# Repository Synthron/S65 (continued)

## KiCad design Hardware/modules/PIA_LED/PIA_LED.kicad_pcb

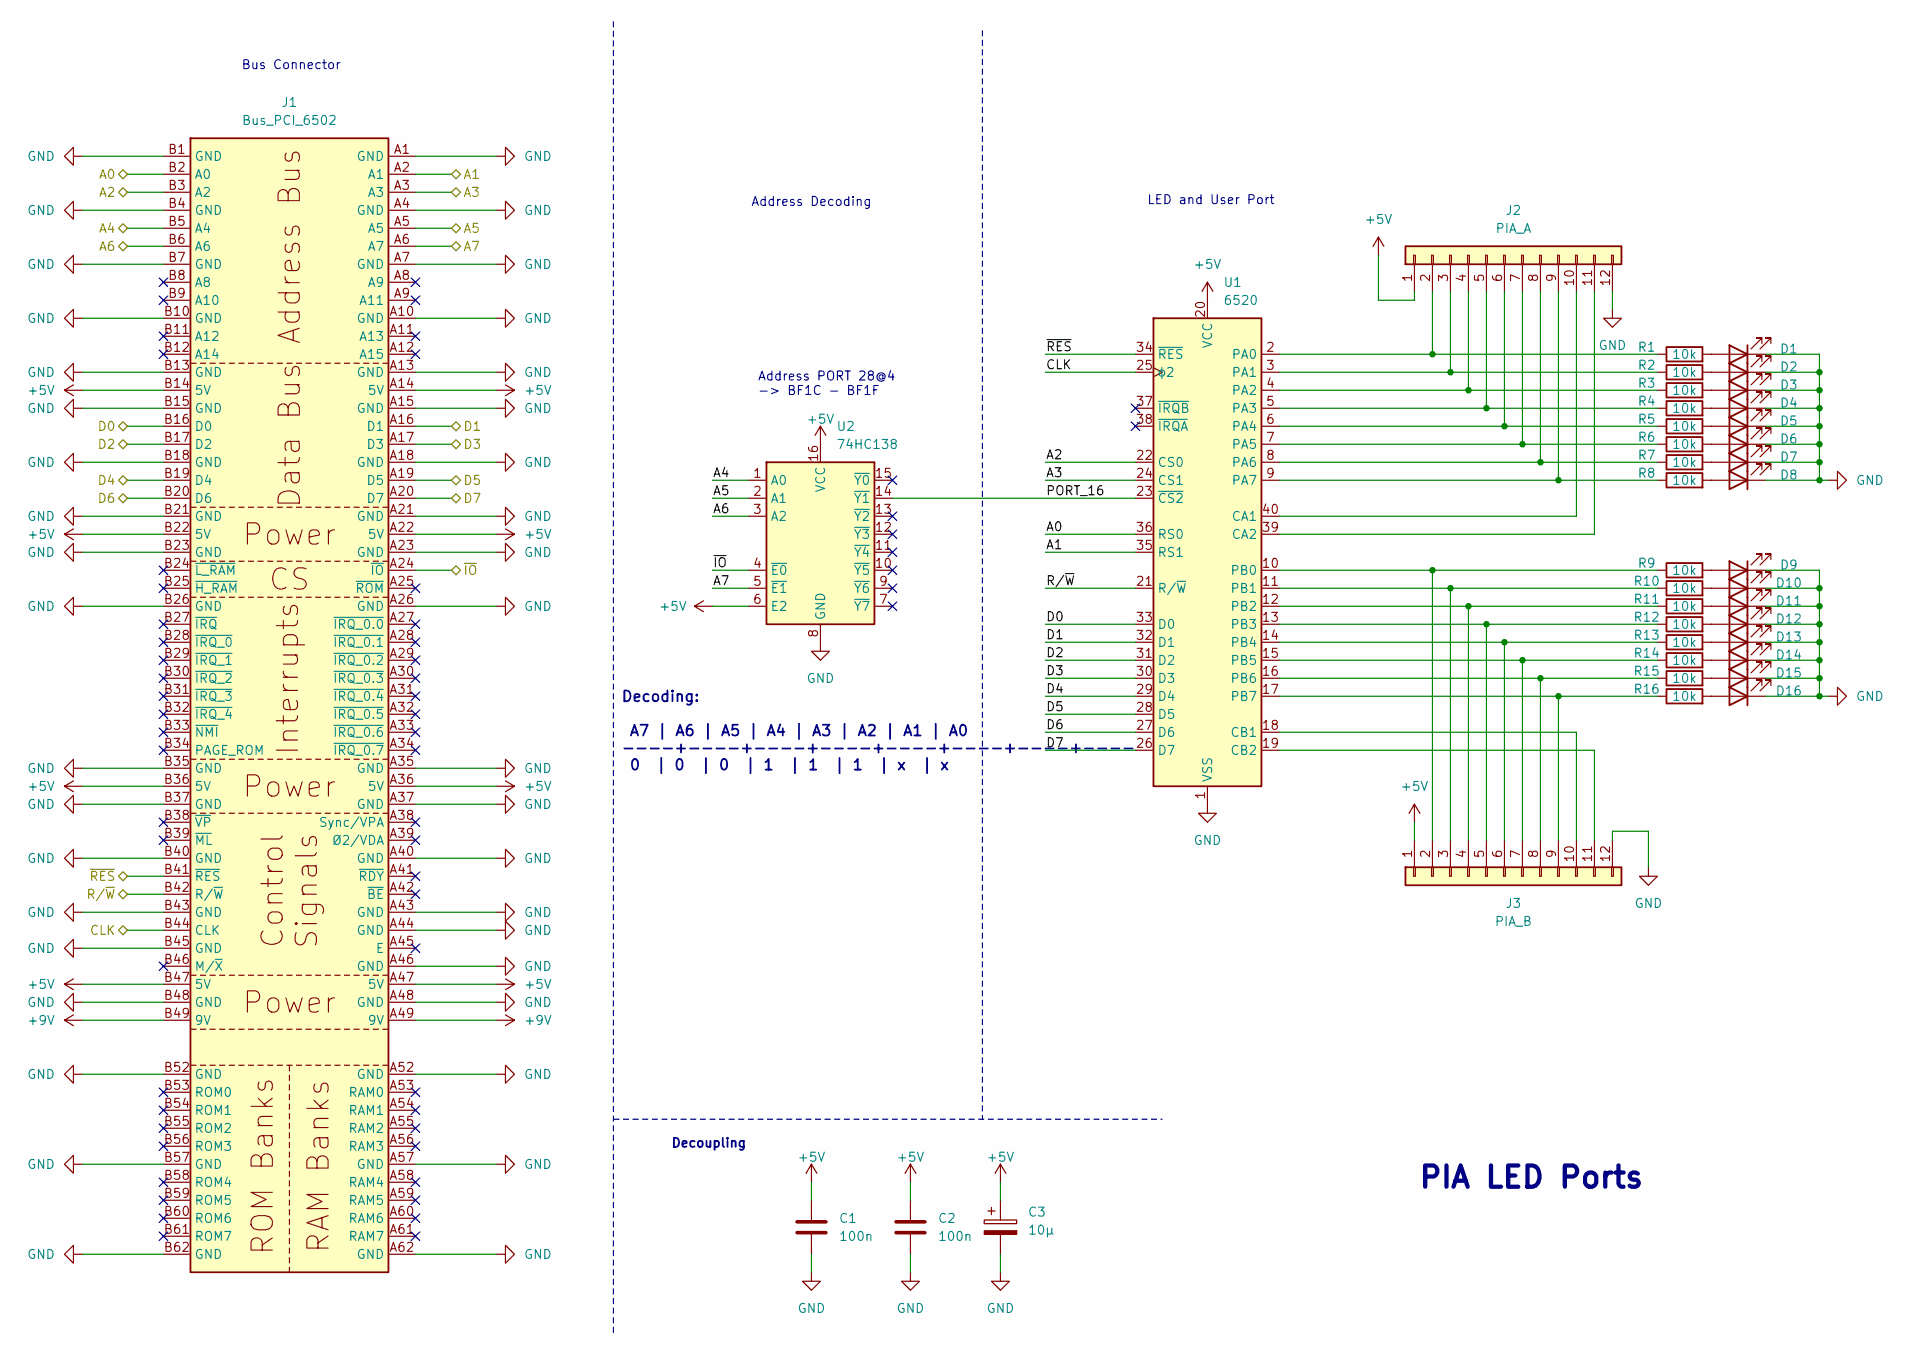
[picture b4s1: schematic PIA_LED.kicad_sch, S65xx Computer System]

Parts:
C1, C2: 100n; C_0805_2012Metric
C3: 10µ; CP_Radial_D5.0mm_P2.50mm
D1, D2, D3, D4, D5, D6, D7, D8, D9, D10, D11, D12, D13, D14, D15, D16: LED; SPST_Edge
J1: Bus_PCI_6502; BUS_PCI
J2: PIA_A; PinHeader_1x12_P2.54mm_Vertical
J3: PIA_B; PinHeader_1x12_P2.54mm_Vertical
R1, R2, R3, R4, R5, R6, R7, R8, R9, R10, R11, R12, R13, R14, R15, R16: 10k; R_0805_2012Metric
U1: 6520; DIP-40_W15.24mm
U2: 74HC138; DIP-16_W7.62mm_LongPads

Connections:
+5V: C1.1, C2.1, C3.1, J1.A14 (5V), J1.A22 (5V), J1.A36 (5V), J1.A47 (5V), J1.B14 (5V), J1.B22 (5V), J1.B36 (5V), J1.B47 (5V), J2.1, J3.1, U1.20 (VCC), U2.6 (E2), U2.16 (VCC)
+9V: J1.A49 (9V), J1.B49 (9V)
/A0: J1.B2 (A0), U1.36 (RS0)
/A1: J1.A2 (A1), U1.35 (RS1)
/A2: J1.B3 (A2), U1.22 (CS0)
/A3: J1.A3, U1.24 (CS1)
/A4: J1.B5 (A4), U2.1 (A0)
/A5: J1.A5, U2.2 (A1)
/A6: J1.B6 (A6), U2.3 (A2)
/A7: J1.A6 (A7), U2.5 (~E1)
/CLK: J1.B44 (CLK), U1.25 (ϕ2)
/D0: J1.B16 (D0), U1.33 (D0)
/D1: J1.A16 (D1), U1.32 (D1)
/D2: J1.B17 (D2), U1.31 (D2)
/D3: J1.A17 (D3), U1.30 (D3)
/D4: J1.B19 (D4), U1.29 (D4)
/D5: J1.A19 (D5), U1.28 (D5)
/D6: J1.B20 (D6), U1.27 (D6)
/D7: J1.A20 (D7), U1.26 (D7)
/PORT_16: U1.23 (~CS2), U2.14 (~Y1)
/R/~W: J1.B42 (R/~W), U1.21 (R/~W)
/~IO: J1.A24 (~IO), U2.4 (~E0)
/~RES: J1.B41 (~RES), U1.34 (~RES)
GND: C1.2, C2.2, C3.2, D1.1 (K), D2.1 (K), D3.1 (K), D4.1 (K), D5.1 (K), D6.1 (K), D7.1 (K), D8.1 (K), D9.1 (K), D10.1 (K), D11.1 (K), D12.1 (K), D13.1 (K), D14.1 (K), D15.1 (K), D16.1 (K), J1.A1 (GND), J1.A4 (GND), J1.A7 (GND), J1.A10 (GND), J1.A13 (GND), J1.A15 (GND), J1.A18 (GND), J1.A21 (GND), J1.A23 (GND), J1.A26 (GND), J1.A35 (GND), J1.A37 (GND), J1.A40 (GND), J1.A43 (GND), J1.A44 (GND), J1.A46 (GND), J1.A48 (GND), J1.A52 (GND), J1.A57 (GND), J1.A62 (GND), J1.B1 (GND), J1.B4 (GND), J1.B7 (GND), J1.B10 (GND), J1.B13 (GND), J1.B15 (GND), J1.B18 (GND), J1.B21 (GND), J1.B23 (GND), J1.B26 (GND), J1.B35 (GND), J1.B37 (GND), J1.B40 (GND), J1.B43 (GND), J1.B45 (GND), J1.B48 (GND), J1.B52 (GND), J1.B57 (GND), J1.B62 (GND), J2.12, J3.12, U1.1 (VSS), U2.8 (GND)
unnamed: D1.2 (A), R1.2
unnamed: D2.2 (A), R2.2
unnamed: D3.2 (A), R3.2
unnamed: D4.2 (A), R4.2
unnamed: D5.2 (A), R5.2
unnamed: D6.2 (A), R6.2
unnamed: D7.2 (A), R7.2
unnamed: D8.2 (A), R8.2
unnamed: D9.2 (A), R9.2
unnamed: D10.2 (A), R10.2
unnamed: D11.2 (A), R11.2
unnamed: D12.2 (A), R12.2
unnamed: D13.2 (A), R13.2
unnamed: D14.2 (A), R14.2
unnamed: D15.2 (A), R15.2
unnamed: D16.2 (A), R16.2
unnamed: J2.2, R1.1, U1.2 (PA0)
unnamed: J2.3, R2.1, U1.3 (PA1)
unnamed: J2.4, R3.1, U1.4 (PA2)
unnamed: J2.5, R4.1, U1.5 (PA3)
unnamed: J2.6, R5.1, U1.6 (PA4)
unnamed: J2.7, R6.1, U1.7 (PA5)
unnamed: J2.8, R7.1, U1.8 (PA6)
unnamed: J2.9, R8.1, U1.9 (PA7)
unnamed: J2.10, U1.40 (CA1)
unnamed: J2.11, U1.39 (CA2)
unnamed: J3.2, R9.1, U1.10 (PB0)
unnamed: J3.3, R10.1, U1.11 (PB1)
unnamed: J3.4, R11.1, U1.12 (PB2)
unnamed: J3.5, R12.1, U1.13 (PB3)
unnamed: J3.6, R13.1, U1.14 (PB4)
unnamed: J3.7, R14.1, U1.15 (PB5)
unnamed: J3.8, R15.1, U1.16 (PB6)
unnamed: J3.9, R16.1, U1.17 (PB7)
unnamed: J3.10, U1.18 (CB1)
unnamed: J3.11, U1.19 (CB2)

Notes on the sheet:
Decoding: A7 | A6 | A5 | A4 | A3 | A2 | A1 | A0 ----+----+----+----+----+----+----+---- 0 | 0 | 0 | 1 | 1 | 1 | x | x
PIA LED Ports
Address PORT 28@4 -> BF1C - BF1F
Address Decoding
Bus Connector
Decoupling
LED and User Port

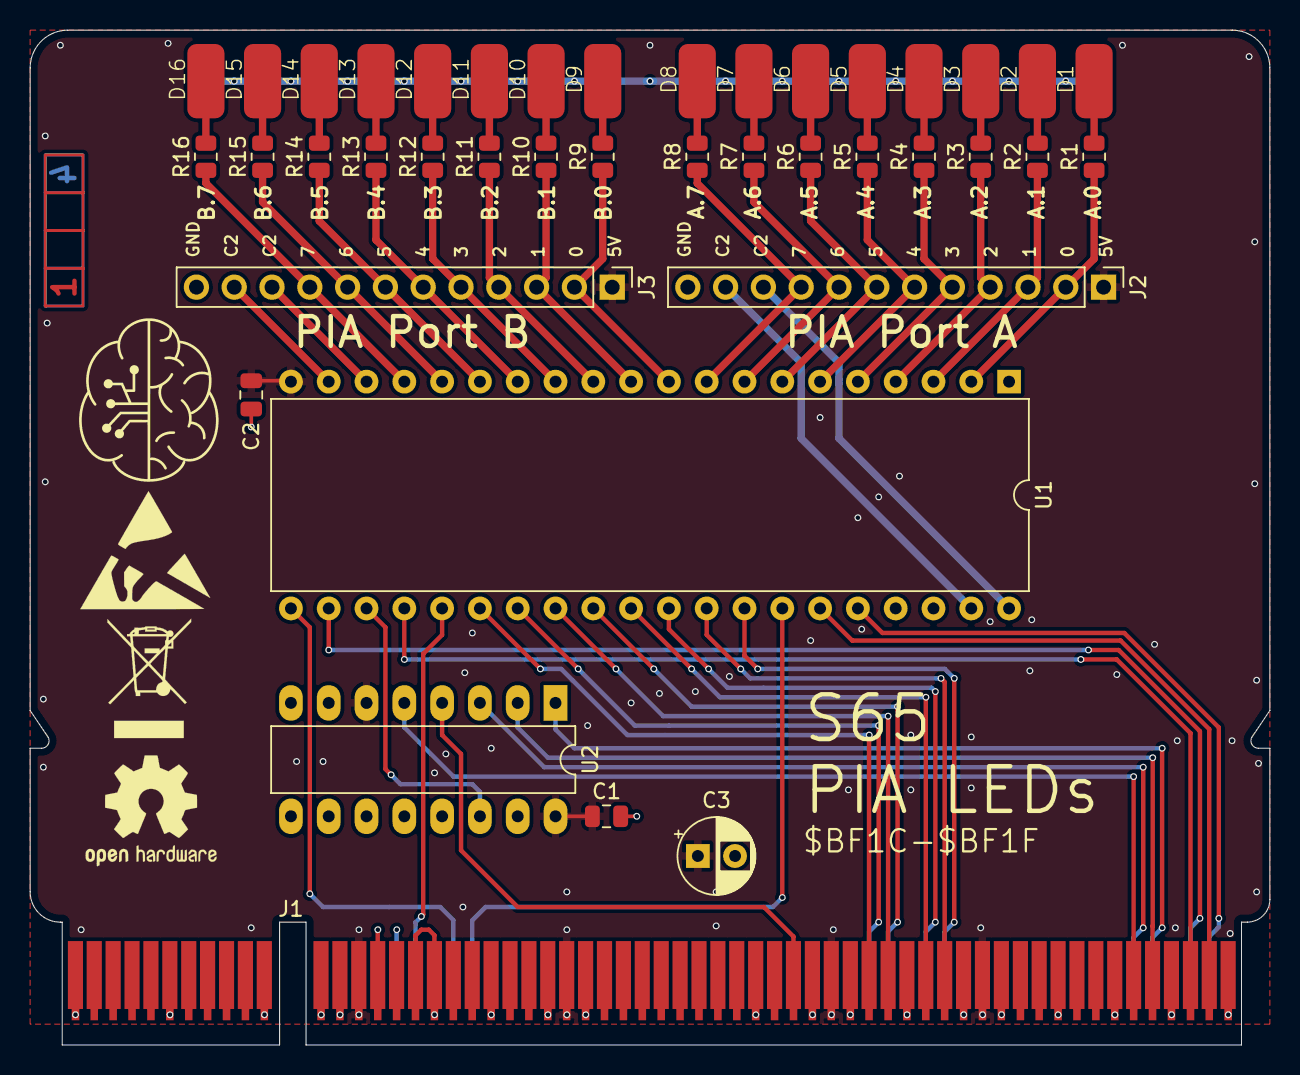
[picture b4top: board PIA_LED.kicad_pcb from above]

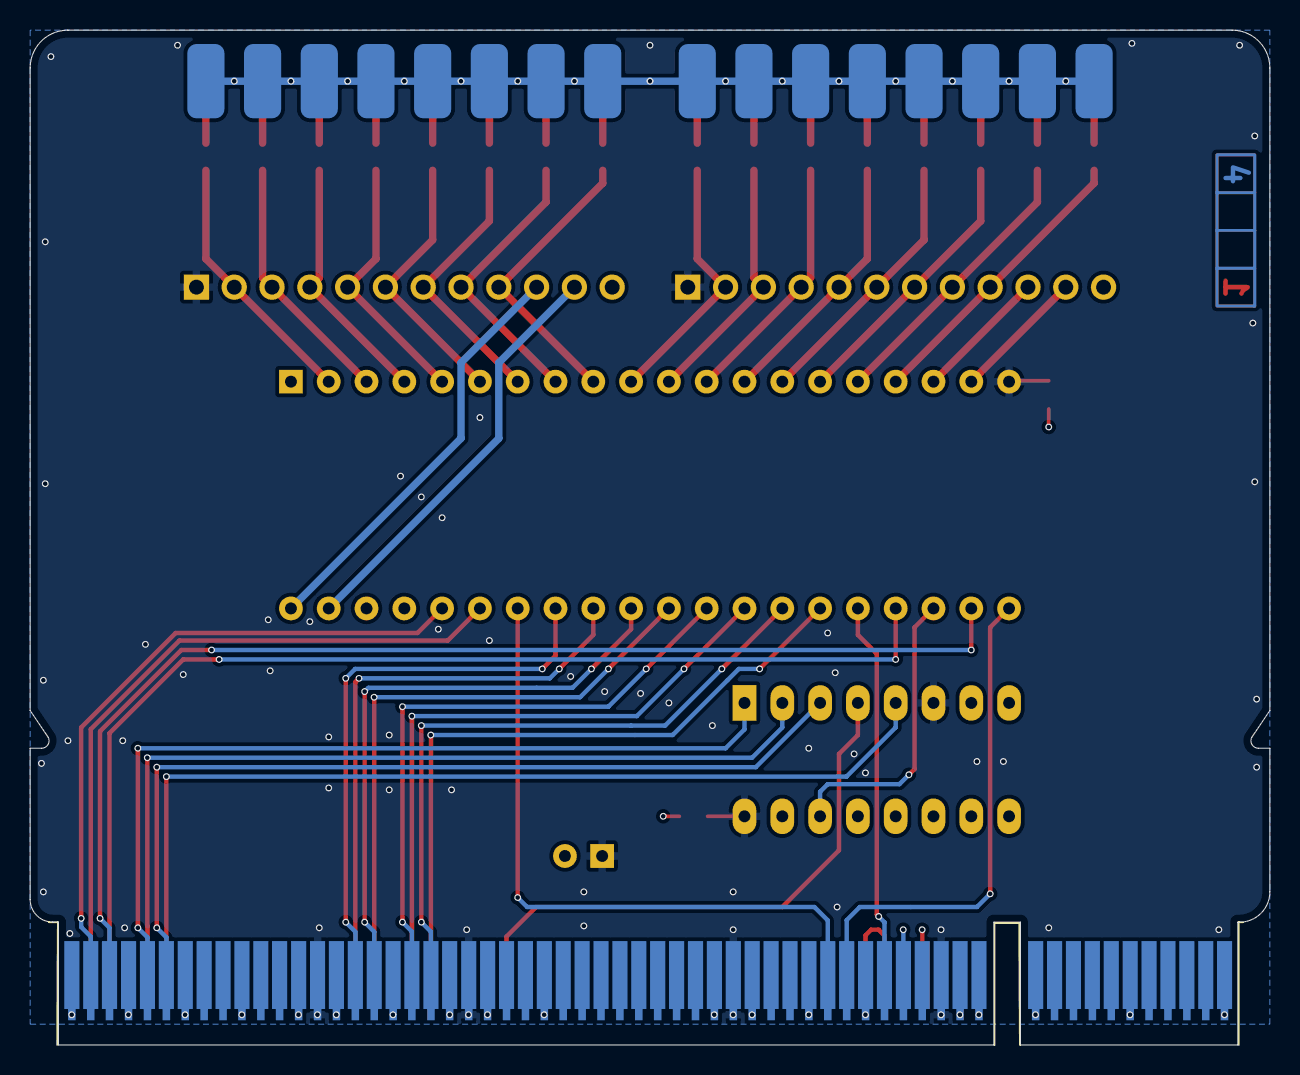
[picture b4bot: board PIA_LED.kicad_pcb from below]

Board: 4 copper layers, 83.3 x 68.2 mm, 41 parts (17 on the bottom side), 60 nets.

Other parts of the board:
Ref**: Val**; ladder_4

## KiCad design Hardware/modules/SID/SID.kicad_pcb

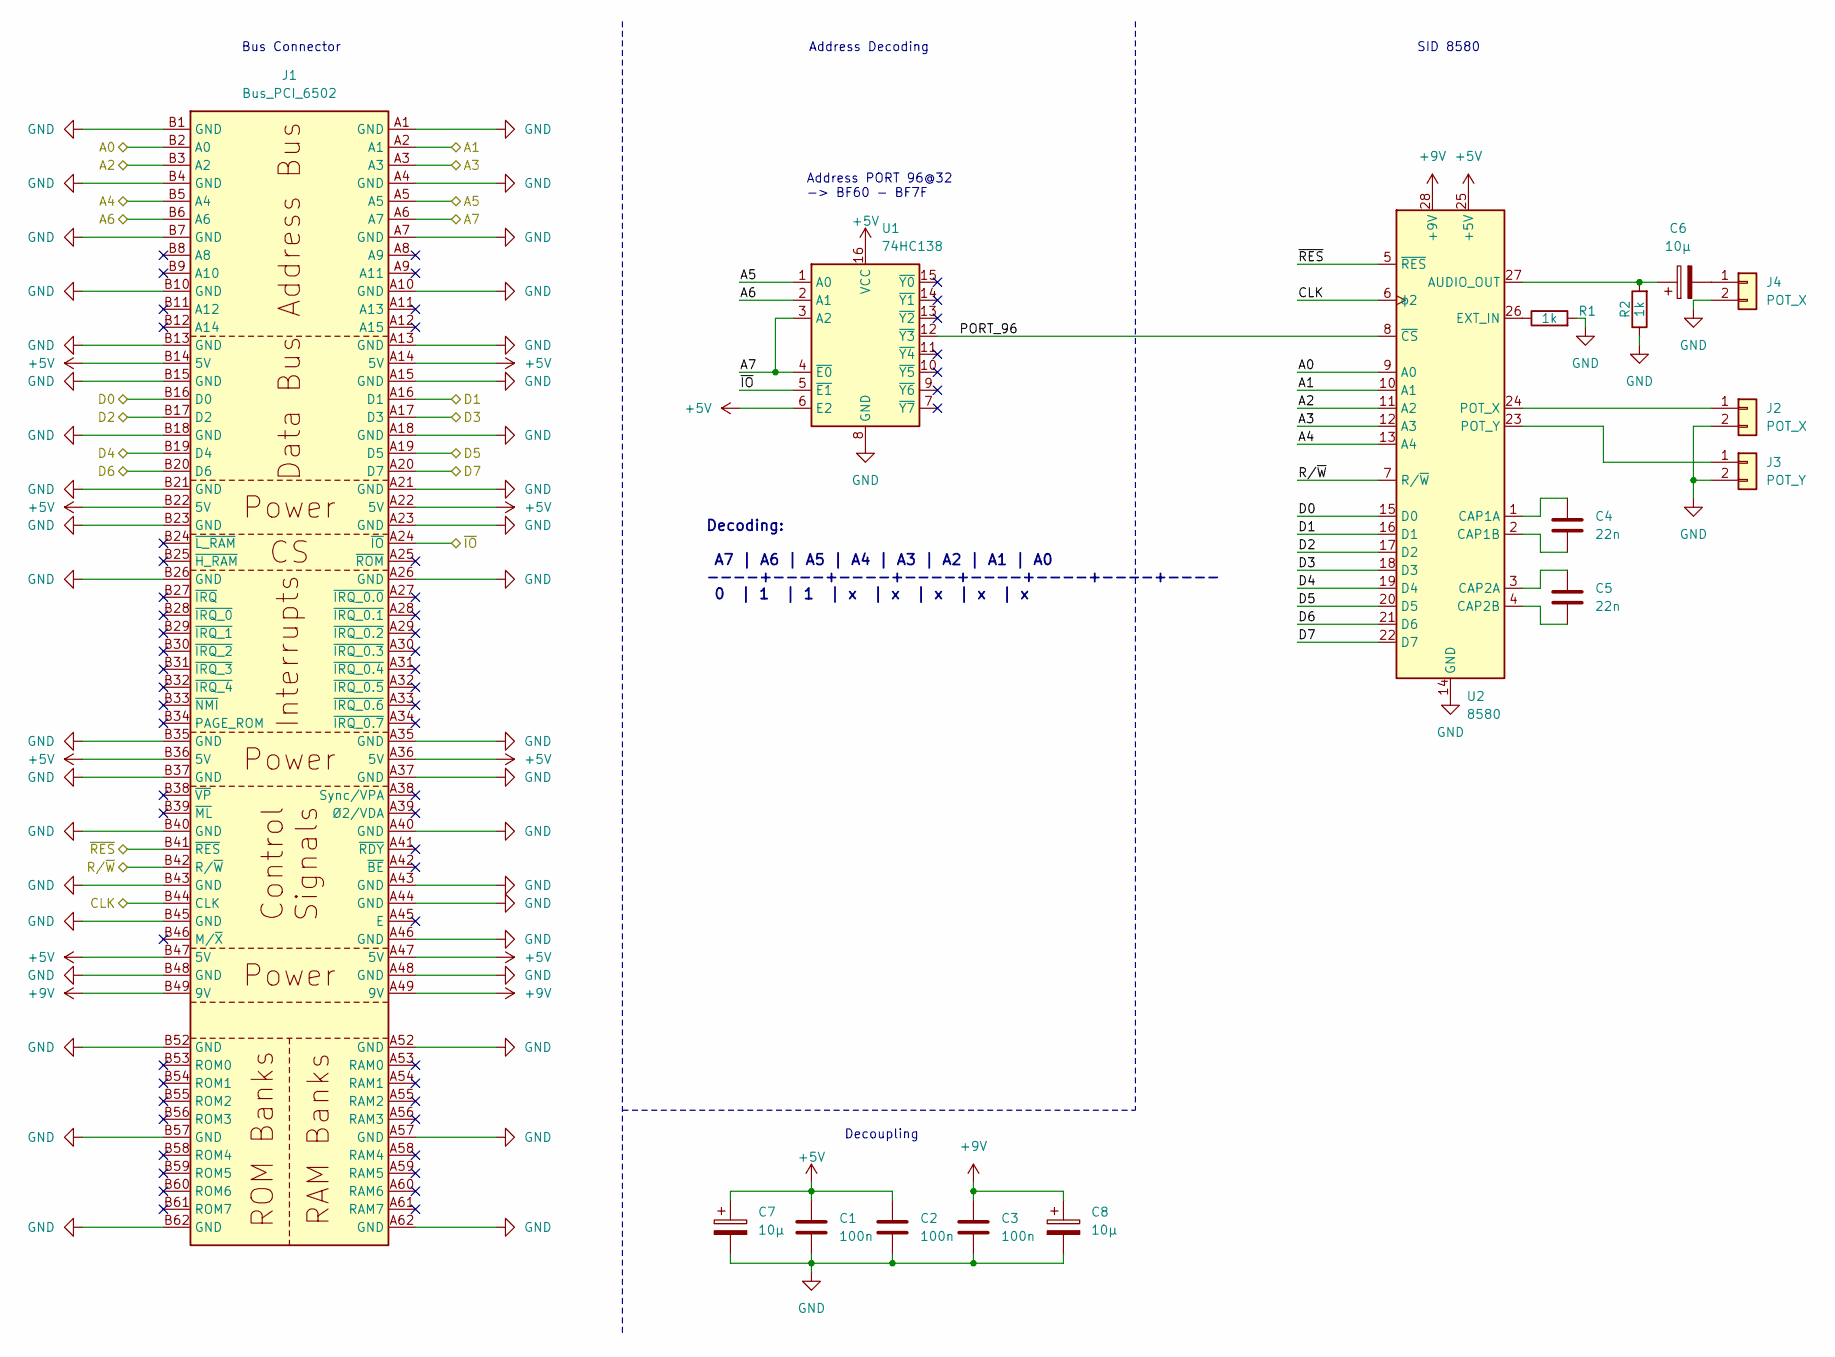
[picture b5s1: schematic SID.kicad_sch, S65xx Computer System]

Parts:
C1, C2, C3: 100n; C_0805_2012Metric
C4, C5: 22n; C_0805_2012Metric
C6, C7, C8: 10µ; CP_Radial_D5.0mm_P2.50mm
J1: Bus_PCI_6502; BUS_PCI
J2, J4: POT_X; PinHeader_1x02_P2.54mm_Horizontal
J3: POT_Y; PinHeader_1x02_P2.54mm_Horizontal
R1, R2: 1k; R_0805_2012Metric
U1: 74HC138; DIP-16_W7.62mm
U2: 8580; DIP-28_W15.24mm

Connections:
+5V: C1.1, C2.1, C7.1, J1.A14 (5V), J1.A22 (5V), J1.A36 (5V), J1.A47 (5V), J1.B14 (5V), J1.B22 (5V), J1.B36 (5V), J1.B47 (5V), U1.6 (E2), U1.16 (VCC), U2.25 (+5V)
+9V: C3.1, C8.1, J1.A49 (9V), J1.B49 (9V), U2.28 (+9V)
/A0: J1.B2 (A0), U2.9 (A0)
/A1: J1.A2 (A1), U2.10 (A1)
/A2: J1.B3 (A2), U2.11 (A2)
/A3: J1.A3, U2.12 (A3)
/A4: J1.B5 (A4), U2.13 (A4)
/A5: J1.A5, U1.1 (A0)
/A6: J1.B6 (A6), U1.2 (A1)
/A7: J1.A6 (A7), U1.3 (A2), U1.4 (~E0)
/CLK: J1.B44 (CLK), U2.6 (ϕ2)
/D0: J1.B16 (D0), U2.15 (D0)
/D1: J1.A16 (D1), U2.16 (D1)
/D2: J1.B17 (D2), U2.17 (D2)
/D3: J1.A17 (D3), U2.18 (D3)
/D4: J1.B19 (D4), U2.19 (D4)
/D5: J1.A19 (D5), U2.20 (D5)
/D6: J1.B20 (D6), U2.21 (D6)
/D7: J1.A20 (D7), U2.22 (D7)
/PORT_96: U1.12 (~Y3), U2.8 (~CS)
/R/~W: J1.B42 (R/~W), U2.7 (R/~W)
/~IO: J1.A24 (~IO), U1.5 (~E1)
/~RES: J1.B41 (~RES), U2.5 (~RES)
GND: C1.2, C2.2, C3.2, C7.2, C8.2, J1.A1 (GND), J1.A4 (GND), J1.A7 (GND), J1.A10 (GND), J1.A13 (GND), J1.A15 (GND), J1.A18 (GND), J1.A21 (GND), J1.A23 (GND), J1.A26 (GND), J1.A35 (GND), J1.A37 (GND), J1.A40 (GND), J1.A43 (GND), J1.A44 (GND), J1.A46 (GND), J1.A48 (GND), J1.A52 (GND), J1.A57 (GND), J1.A62 (GND), J1.B1 (GND), J1.B4 (GND), J1.B7 (GND), J1.B10 (GND), J1.B13 (GND), J1.B15 (GND), J1.B18 (GND), J1.B21 (GND), J1.B23 (GND), J1.B26 (GND), J1.B35 (GND), J1.B37 (GND), J1.B40 (GND), J1.B43 (GND), J1.B45 (GND), J1.B48 (GND), J1.B52 (GND), J1.B57 (GND), J1.B62 (GND), J2.2, J3.2, J4.2, R1.2, R2.1, U1.8 (GND), U2.14 (GND)
unnamed: J2.1, U2.24 (POT_X)
unnamed: J3.1, U2.23 (POT_Y)
unnamed: C6.2, J4.1
unnamed: C6.1, R2.2, U2.27 (AUDIO_OUT)
unnamed: C4.1, U2.1 (CAP1A)
unnamed: C4.2, U2.2 (CAP1B)
unnamed: C5.1, U2.3 (CAP2A)
unnamed: C5.2, U2.4 (CAP2B)
unnamed: R1.1, U2.26 (EXT_IN)

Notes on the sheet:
Address PORT 96@32 -> BF60 - BF7F
Decoding: A7 | A6 | A5 | A4 | A3 | A2 | A1 | A0 ----+----+----+----+----+----+----+---- 0 | 1 | 1 | x | x | x | x | x
SID 8580
Decoupling
Address Decoding
Bus Connector

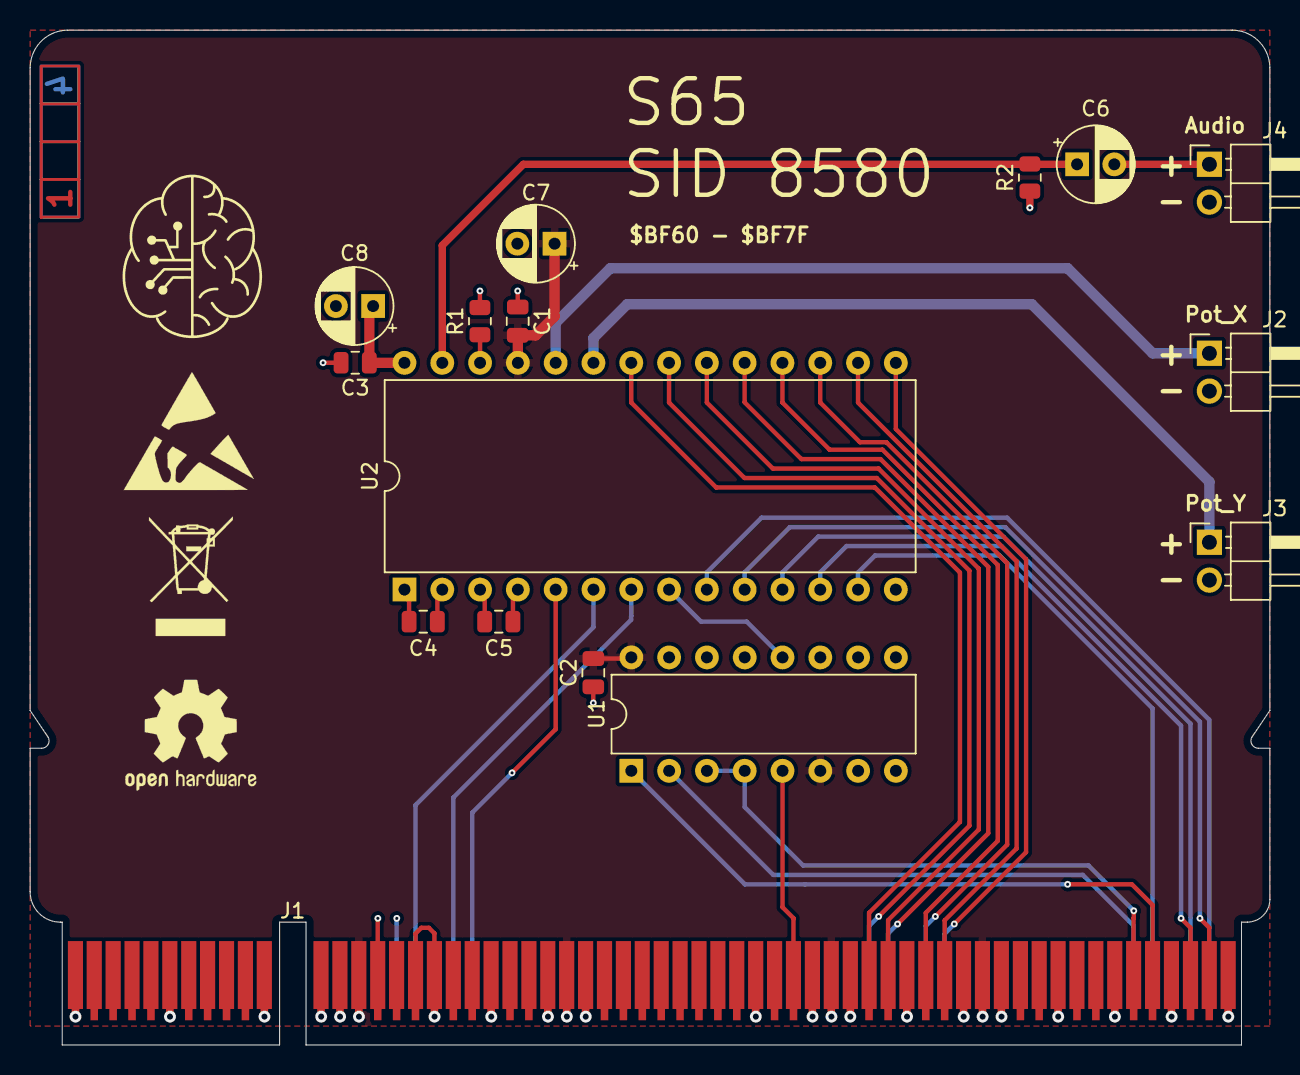
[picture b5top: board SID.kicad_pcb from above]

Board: 4 copper layers, 83.3 x 68.2 mm, 17 parts (1 on the bottom side), 33 nets.

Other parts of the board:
Ref**: Val**; ladder_4

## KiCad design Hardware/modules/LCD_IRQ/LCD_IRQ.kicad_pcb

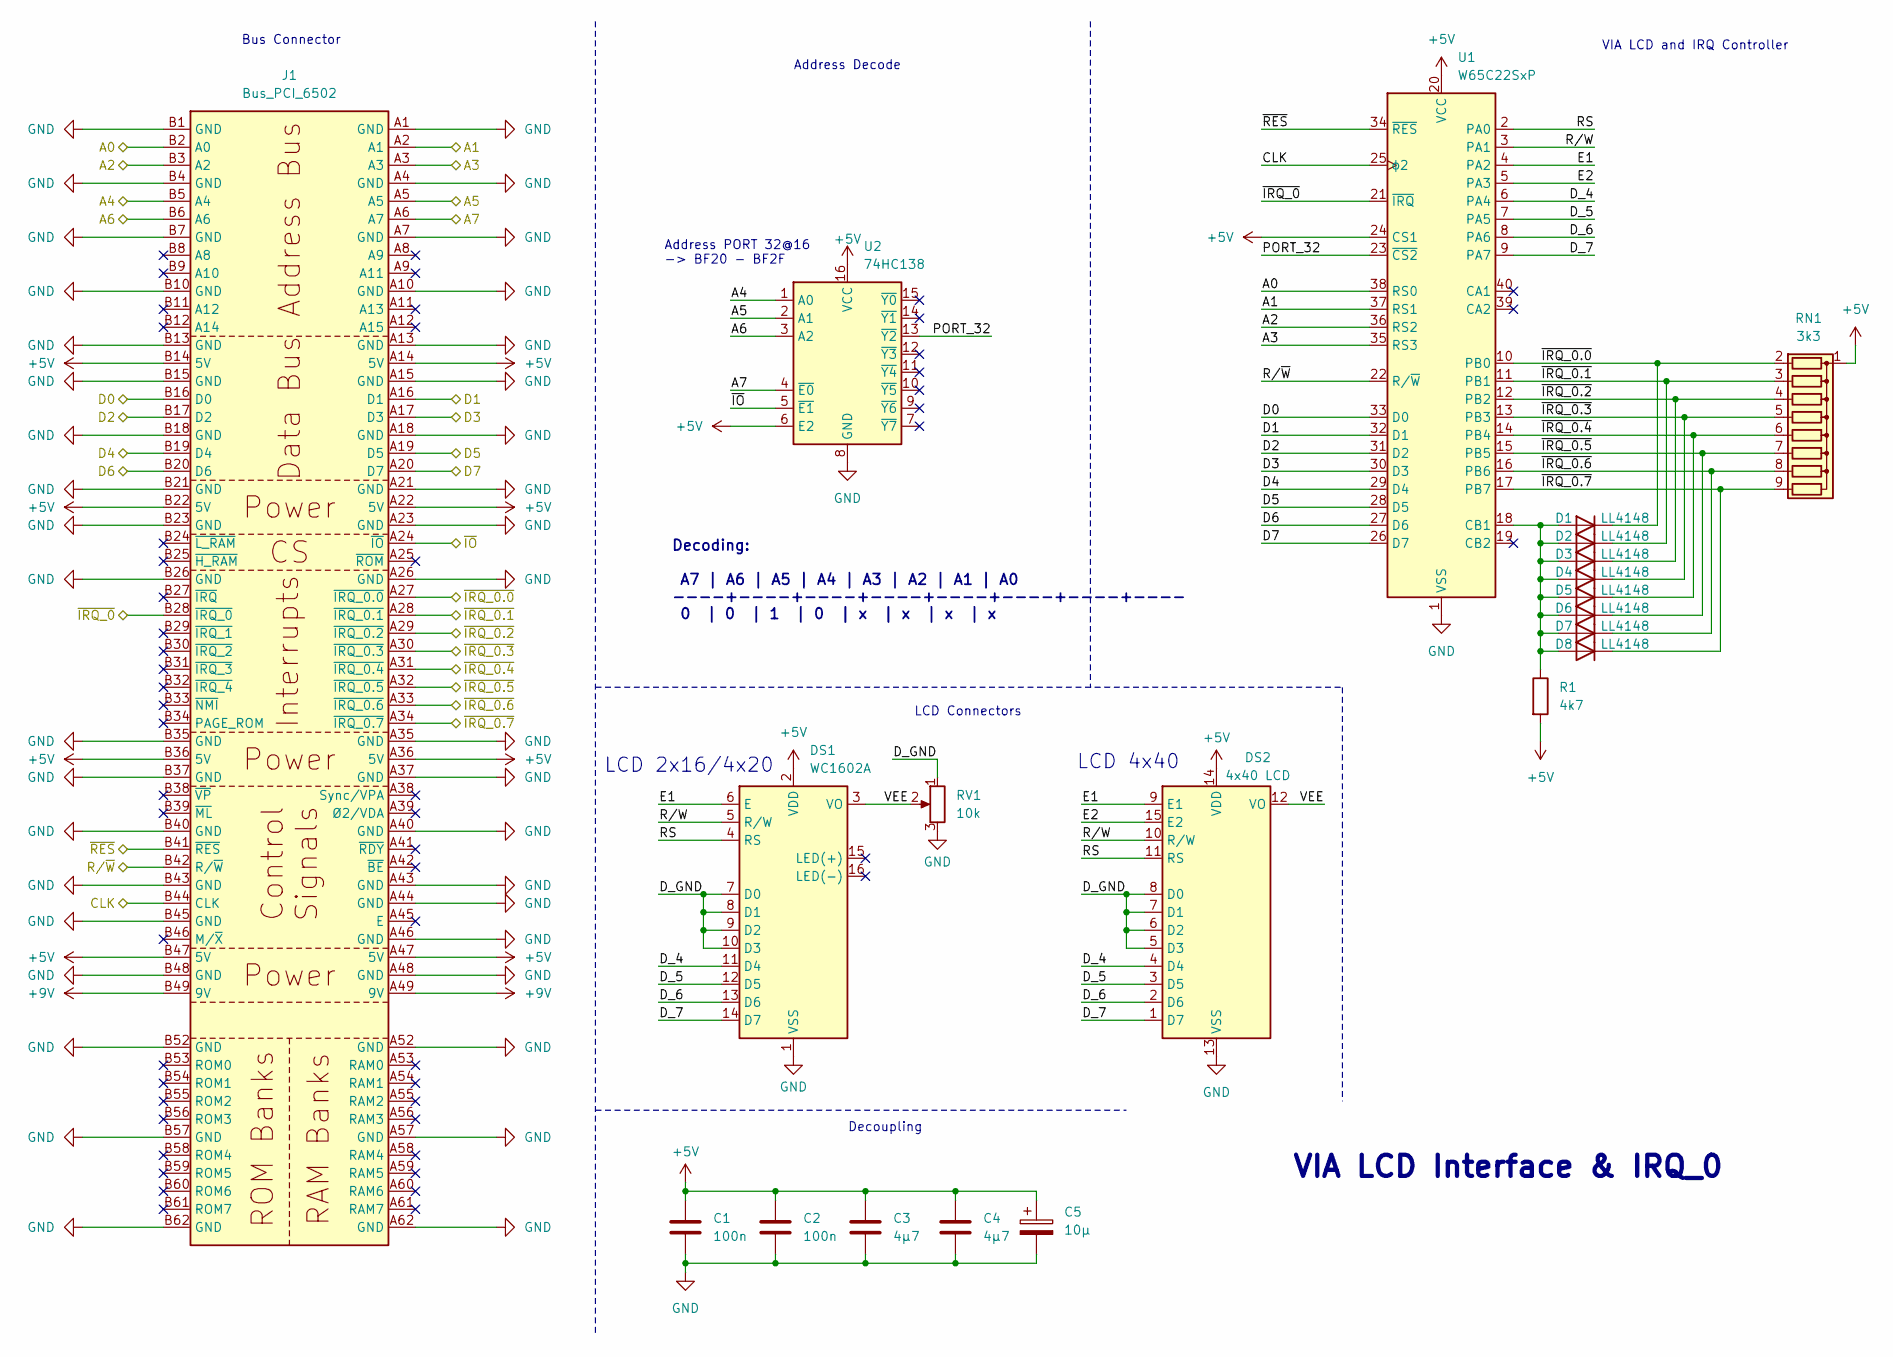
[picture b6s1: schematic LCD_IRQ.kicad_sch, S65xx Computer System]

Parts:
C1, C2: 100n; C_0805_2012Metric
C3, C4: 4µ7; C_0805_2012Metric
C5: 10µ; CP_Radial_D5.0mm_P2.50mm
D1, D2, D3, D4, D5, D6, D7, D8: LL4148; D_MiniMELF
DS1: WC1602A; PinHeader_1x16_P2.54mm_Vertical
DS2: 4x40 LCD; PinHeader_2x08_P2.54mm_Vertical
J1: Bus_PCI_6502; BUS_PCI
R1: 4k7; R_0805_2012Metric
RN1: 3k3; R_Array_SIP9
RV1: 10k; Potentiometer_Bourns_TC33X_Vertical
U1: W65C22SxP; DIP-40_W15.24mm
U2: 74HC138; DIP-16_W7.62mm

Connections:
+5V: C1.1, C2.1, C3.1, C4.1, C5.1, DS1.2 (VDD), DS2.14 (VDD), J1.A14 (5V), J1.A22 (5V), J1.A36 (5V), J1.A47 (5V), J1.B14 (5V), J1.B22 (5V), J1.B36 (5V), J1.B47 (5V), R1.2, RN1.1 (common), U1.20 (VCC), U1.24 (CS1), U2.6 (E2), U2.16 (VCC)
+9V: J1.A49 (9V), J1.B49 (9V)
/A0: J1.B2 (A0), U1.38 (RS0)
/A1: J1.A2 (A1), U1.37 (RS1)
/A2: J1.B3 (A2), U1.36 (RS2)
/A3: J1.A3, U1.35 (RS3)
/A4: J1.B5 (A4), U2.1 (A0)
/A5: J1.A5, U2.2 (A1)
/A6: J1.B6 (A6), U2.3 (A2)
/A7: J1.A6 (A7), U2.4 (~E0)
/CLK: J1.B44 (CLK), U1.25 (ϕ2)
/D0: J1.B16 (D0), U1.33 (D0)
/D1: J1.A16 (D1), U1.32 (D1)
/D2: J1.B17 (D2), U1.31 (D2)
/D3: J1.A17 (D3), U1.30 (D3)
/D4: J1.B19 (D4), U1.29 (D4)
/D5: J1.A19 (D5), U1.28 (D5)
/D6: J1.B20 (D6), U1.27 (D6)
/D7: J1.A20 (D7), U1.26 (D7)
/D_4: DS1.11 (D4), DS2.4 (D4), U1.6 (PA4)
/D_5: DS1.12 (D5), DS2.3 (D5), U1.7 (PA5)
/D_6: DS1.13 (D6), DS2.2 (D6), U1.8 (PA6)
/D_7: DS1.14 (D7), DS2.1 (D7), U1.9 (PA7)
/D_GND: DS1.7 (D0), DS1.8 (D1), DS1.9 (D2), DS1.10 (D3), DS2.5 (D3), DS2.6 (D2), DS2.7 (D1), DS2.8 (D0), RV1.1
/E1: DS1.6 (E), DS2.9 (E1), U1.4 (PA2)
/E2: DS2.15 (E2), U1.5 (PA3)
/PORT_32: U1.23 (~CS2), U2.13 (~Y2)
/RS: DS1.4 (RS), DS2.11 (RS), U1.2 (PA0)
/R/W: DS1.5 (R/W), DS2.10 (R/W), U1.3 (PA1)
/R/~W: J1.B42 (R/~W), U1.22 (R/~W)
/VEE: DS1.3 (VO), DS2.12 (VO), RV1.2
/~IO: J1.A24 (~IO), U2.5 (~E1)
/~IRQ_0.0: D1.1 (K), J1.A27 (~IRQ_0.0), RN1.2 (R1), U1.10 (PB0)
/~IRQ_0.1: D2.1 (K), J1.A28 (~IRQ_0.1), RN1.3 (R2), U1.11 (PB1)
/~IRQ_0.2: D3.1 (K), J1.A29 (~IRQ_0.2), RN1.4 (R3), U1.12 (PB2)
/~IRQ_0.3: D4.1 (K), J1.A30 (~IRQ_0.3), RN1.5 (R4), U1.13 (PB3)
/~IRQ_0.4: D5.1 (K), J1.A31 (~IRQ_0.4), RN1.6 (R5), U1.14 (PB4)
/~IRQ_0.5: D6.1 (K), J1.A32 (~IRQ_0.5), RN1.7 (R6), U1.15 (PB5)
/~IRQ_0.6: D7.1 (K), J1.A33 (~IRQ_0.6), RN1.8 (R7), U1.16 (PB6)
/~IRQ_0.7: D8.1 (K), J1.A34 (~IRQ_0.7), RN1.9 (R8), U1.17 (PB7)
/~IRQ_0: J1.B28 (~IRQ_0), U1.21 (~IRQ)
/~RES: J1.B41 (~RES), U1.34 (~RES)
GND: C1.2, C2.2, C3.2, C4.2, C5.2, DS1.1 (VSS), DS2.13 (VSS), J1.A1 (GND), J1.A4 (GND), J1.A7 (GND), J1.A10 (GND), J1.A13 (GND), J1.A15 (GND), J1.A18 (GND), J1.A21 (GND), J1.A23 (GND), J1.A26 (GND), J1.A35 (GND), J1.A37 (GND), J1.A40 (GND), J1.A43 (GND), J1.A44 (GND), J1.A46 (GND), J1.A48 (GND), J1.A52 (GND), J1.A57 (GND), J1.A62 (GND), J1.B1 (GND), J1.B4 (GND), J1.B7 (GND), J1.B10 (GND), J1.B13 (GND), J1.B15 (GND), J1.B18 (GND), J1.B21 (GND), J1.B23 (GND), J1.B26 (GND), J1.B35 (GND), J1.B37 (GND), J1.B40 (GND), J1.B43 (GND), J1.B45 (GND), J1.B48 (GND), J1.B52 (GND), J1.B57 (GND), J1.B62 (GND), RV1.3, U1.1 (VSS), U2.8 (GND)
unnamed: D1.2 (A), D2.2 (A), D3.2 (A), D4.2 (A), D5.2 (A), D6.2 (A), D7.2 (A), D8.2 (A), R1.1, U1.18 (CB1)

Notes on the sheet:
VIA LCD Interface & IRQ_0
LCD 4x40
VIA LCD and IRQ Controller
Decoupling
LCD 2x16/4x20
Decoding: A7 | A6 | A5 | A4 | A3 | A2 | A1 | A0 ----+----+----+----+----+----+----+---- 0 | 0 | 1 | 0 | x | x | x | x
Bus Connector
LCD Connectors
Address PORT 32@16 -> BF20 - BF2F
Address Decode

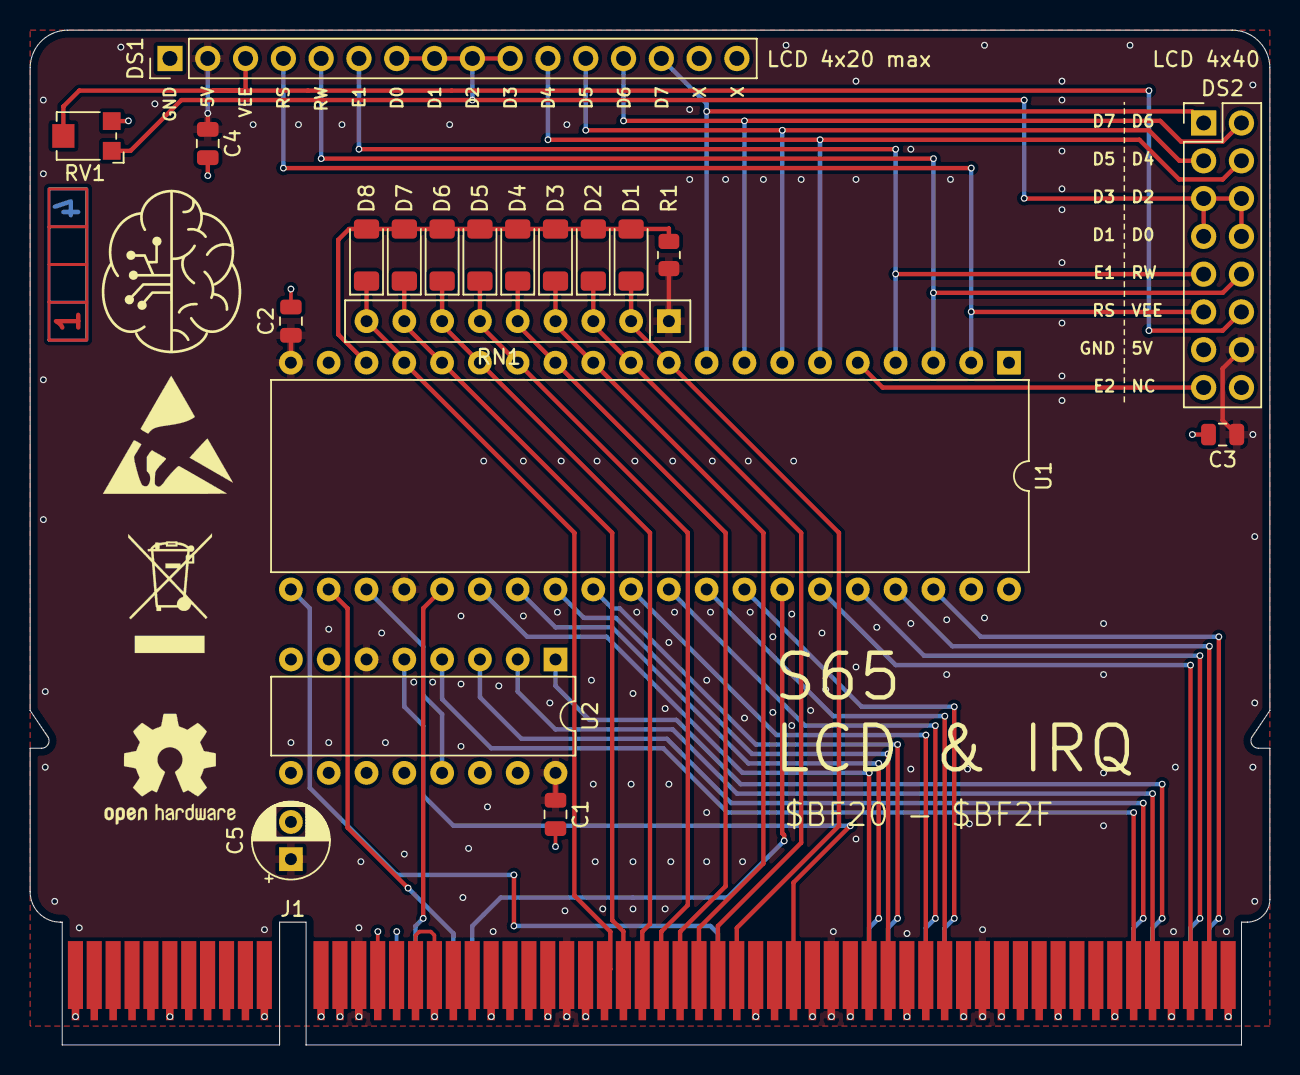
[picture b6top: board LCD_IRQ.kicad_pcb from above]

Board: 4 copper layers, 83.3 x 68.2 mm, 22 parts (1 on the bottom side), 44 nets.

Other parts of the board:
Ref**: Val**; ladder_4
